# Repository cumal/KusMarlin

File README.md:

# Krotos3D

Custom [Marlin](https://github.com/MarlinFirmware/Marlin) firmware for [Krotos3d](https://kustomizit.com/build-your-own-3d-printer/) printer

## New Gcode
```
M777 - HW bed leveling
```
New custom gcode to use the 4-motor Z axis for bed leveling

## Remarkable commands
```
G28 - Auto Home
G29 - Bed Leveling
M80 - Power On PSU
M81 - Power Off PSU
M114 - Get Current Position
M420 - Bed Leveling State
M500 - Save Settings
M503 - Report Settings
M851 - XYZ Probe Offset
```

## Tips
```
M420 S1 - before printing enables bed leveling
M851 Z-X.XX - sets nozzle diff
```

## Configure nozzle height
```
M777 - HW bed leveling
G29 - Bed leveling
G28 Z - Home z at center
G91 - Relative positioning
G1 Z-0.1 - Move up the bed until it touches the nozzle
M114 - Get the Z height X.XX
M851 Z-X.XX - Set the nozzle height to X.XX
```

## Updated files

1. M777.cpp
   - Added custom gcode
2. pins_RAMPS.h
   - Added z axis motors pins
3. gcode.h
   - Added M777
4. gcode.cpp
   - Added 777
5. configuration.h
   - Updated e driver to drv8825
   - Z_MIN_ENDSTOP_INVERTING to true
   - Z_MIN_PROBE_ENDSTOP_INVERTING to true
   - DEFAULT_AXIS_STEPS_PER_UNIT to { 400, 400, 400, 98 }
   - DEFAULT_MAX_ACCELERATION to { 100, 50, 25, 10000 }
   - Update ACCELERATION
   - define USE_PROBE_FOR_Z_HOMING
   - define FIX_MOUNTED_PROBE

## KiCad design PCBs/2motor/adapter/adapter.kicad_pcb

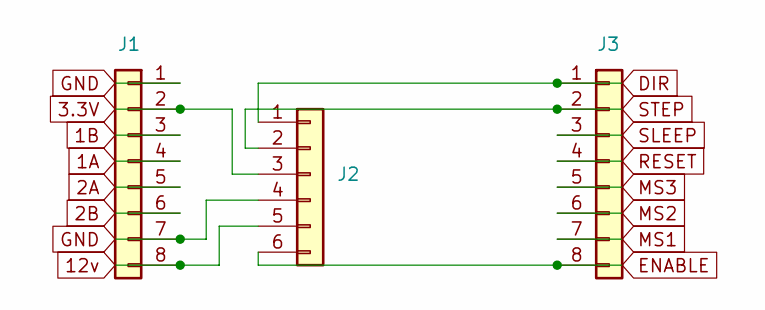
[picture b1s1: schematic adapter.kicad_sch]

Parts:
J1, J3: Conn_01x08; PinHeader_1x08_P2.54mm_Vertical
J2: Conn_01x06; PinSocket_1x06_P2.54mm_Vertical

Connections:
1A: J1.4
1B: J1.3
2A: J1.5
2B: J1.6
3.3V: J1.2, J2.3
12v: J1.8, J2.5
DIR: J2.1, J3.1
ENABLE: J2.6, J3.8
GND: J1.1, J1.7, J2.4
MS1: J3.7
MS2: J3.6
MS3: J3.5
RESET: J3.4
SLEEP: J3.3
STEP: J2.2, J3.2

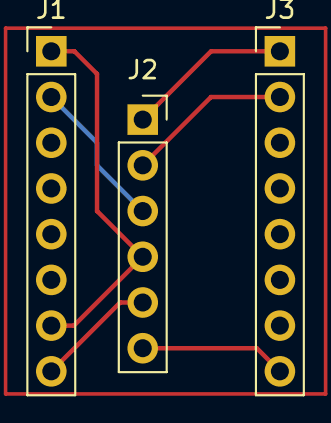
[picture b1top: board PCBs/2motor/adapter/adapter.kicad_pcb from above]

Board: 2 copper layers, 3 parts (0 on the bottom side), 6 nets.

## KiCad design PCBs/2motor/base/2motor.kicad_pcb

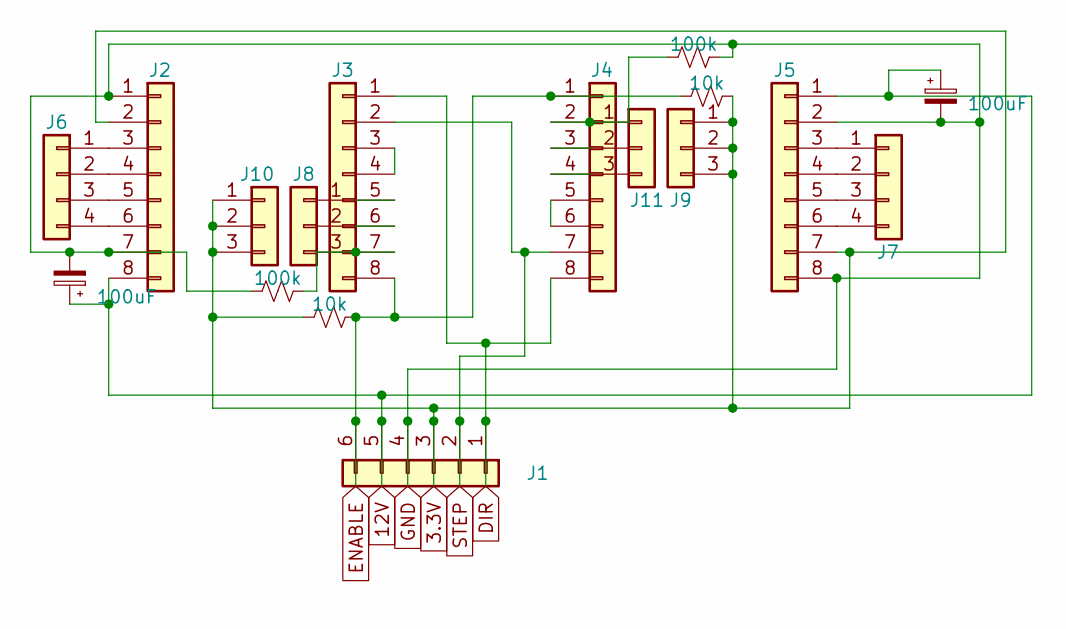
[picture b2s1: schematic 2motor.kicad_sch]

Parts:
C1, C2: 100uF; CP_Radial_D5.0mm_P2.50mm
J1: Conn_01x06; PinSocket_1x06_P2.54mm_Vertical
J2, J3, J4, J5: Conn_01x08; PinSocket_1x08_P2.54mm_Vertical
J6, J7: Conn_01x04; PinHeader_1x04_P2.54mm_Vertical
J8, J9, J10, J11: Conn_01x03; PinHeader_1x03_P2.54mm_Vertical
R1, R3: 100k; R_Axial_DIN0204_L3.6mm_D1.6mm_P7.62mm_Horizontal
R2, R4: 10k; R_Axial_DIN0204_L3.6mm_D1.6mm_P7.62mm_Horizontal

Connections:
3.3V: J1.3, J2.2, J5.7, J9.1, J9.2, J9.3, J10.1, J10.2, J10.3, R2.2, R4.1
12V: C1.1, C2.1, J1.5, J2.8, J5.1
DIR: J1.1, J3.1, J4.8
ENABLE: J1.6, J3.8, J4.1, R2.1, R4.2
GND: C1.2, C2.2, J1.4, J2.1, J2.7, J5.2, J5.8, R1.2, R3.1
unnamed: J2.3, J6.1
unnamed: J2.4, J6.2
unnamed: J2.5, J6.3
unnamed: J2.6, J6.4
unnamed: J3.3, J3.4
unnamed: J3.5, J8.1
unnamed: J3.6, J8.2
unnamed: J4.5, J4.6
unnamed: J5.3, J7.1
unnamed: J5.4, J7.2
unnamed: J5.5, J7.3
unnamed: J5.6, J7.4
unnamed: J3.7, J8.3, R1.1
unnamed: J4.3, J11.2
unnamed: J4.4, J11.3
unnamed: J4.2, J11.1, R3.2
STEP: J1.2, J3.2, J4.7

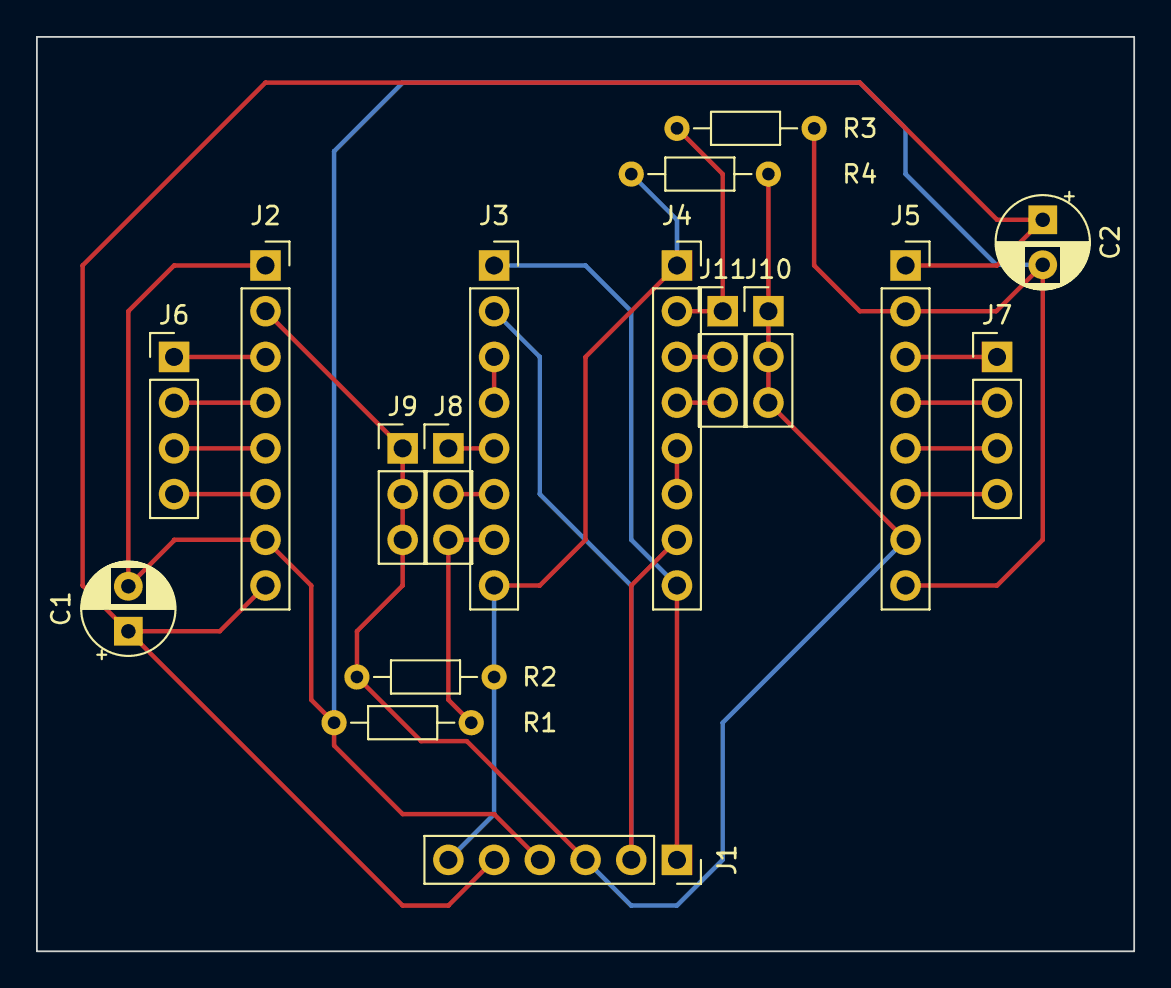
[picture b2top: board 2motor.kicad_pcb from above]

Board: 2 copper layers, 61.0 x 50.8 mm, 17 parts (0 on the bottom side), 22 nets.

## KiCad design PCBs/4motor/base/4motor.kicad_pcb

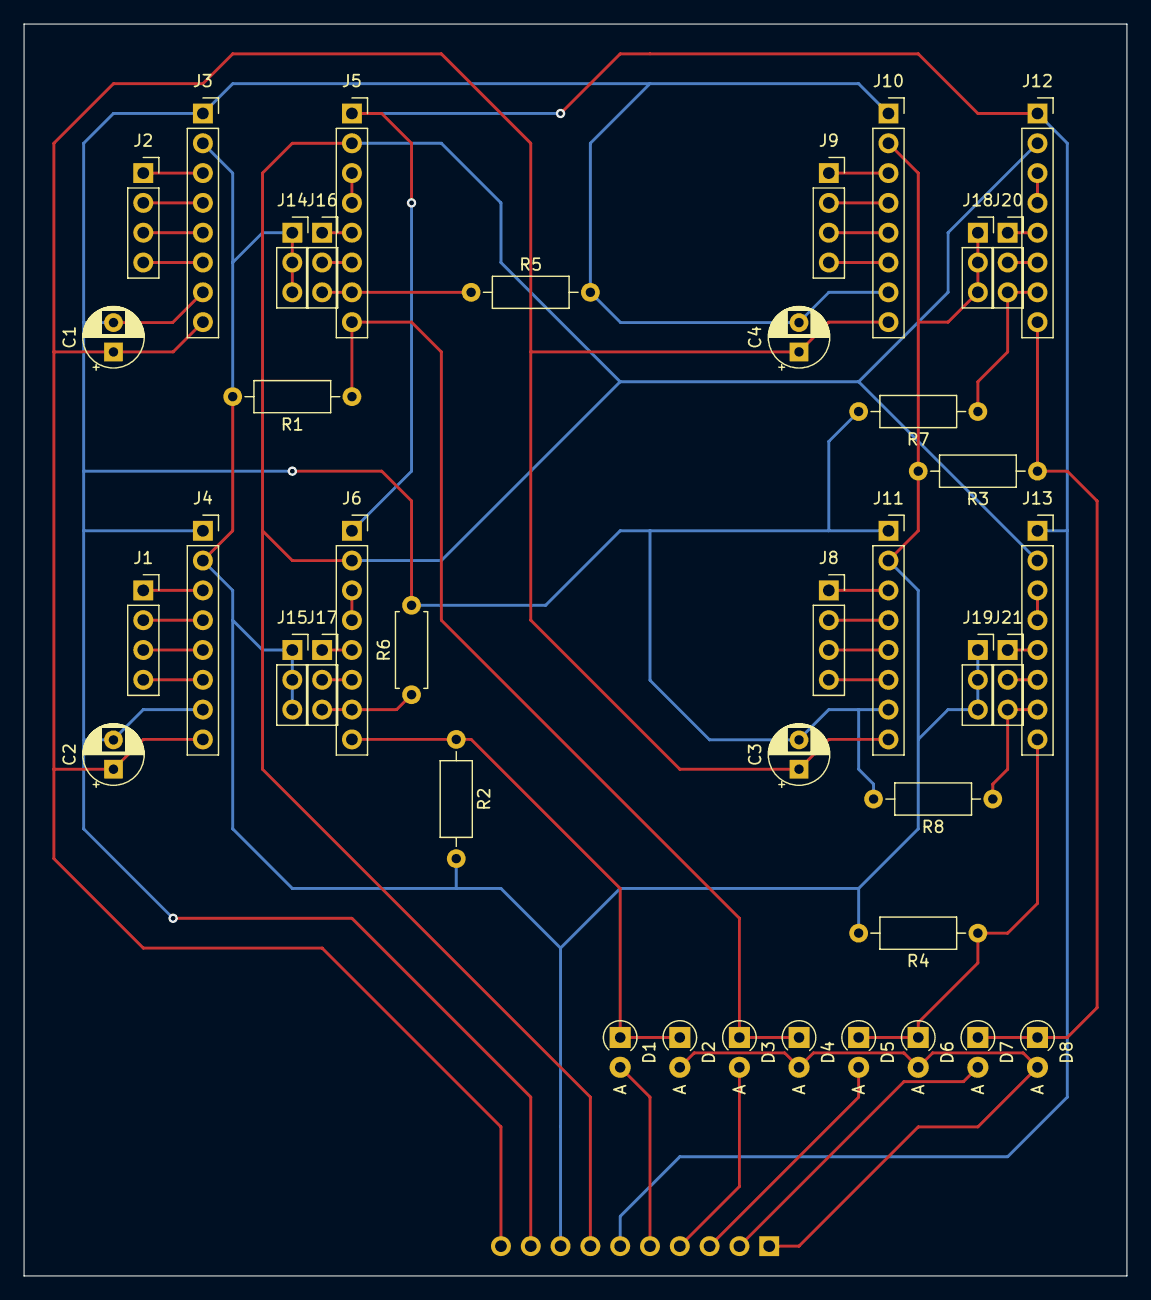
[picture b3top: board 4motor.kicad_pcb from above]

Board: 2 copper layers, 94.0 x 106.7 mm, 41 parts (1 on the bottom side), 46 nets.

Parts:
C1, C2, C3, C4: CP_Small; CP_Radial_D5.0mm_P2.50mm
D1, D2, D3, D4, D5, D6, D7, D8: D; D_A-405_P2.54mm_Vertical_AnodeUp
J1, J2, J8, J9: Conn_01x04_Male; PinSocket_1x04_P2.54mm_Vertical
J3, J4, J5, J6, J10, J11, J12, J13: Conn_01x08; PinSocket_1x08_P2.54mm_Vertical
J7: Conn_01x10; PinSocket_1x10_P2.54mm_Vertical
J14, J15, J16, J17, J18, J19, J20, J21: Conn_01x03; PinSocket_1x03_P2.54mm_Vertical
R1, R2, R3, R4, R5, R7, R8: R_Small_US; R_Axial_DIN0207_L6.3mm_D2.5mm_P10.16mm_Horizontal
R6: R_Small_US; R_Axial_DIN0207_L6.3mm_D2.5mm_P7.62mm_Horizontal

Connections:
3.3V: J3.2, J4.2, J7.8, J10.2, J11.2, J14.1, J14.2, J14.3, J15.1, J15.2, J15.3, J18.1, J18.2, J18.3, J19.1, J19.2, J19.3, R1.2, R2.2, R3.2, R4.2
12V: C1.1, C2.1, C3.1, C4.1, J3.8, J4.8, J7.10, J10.8, J11.8
Dir: J5.1, J6.1, J7.6, J12.1, J13.1
Enable1: D1.2 (A), J7.5
Enable2: D3.2 (A), J7.4
Enable3: D5.2 (A), J7.3
Enable4: D7.2 (A), J7.2
EnableAll: D2.2 (A), D4.2 (A), D6.2 (A), D8.2 (A), J7.1
GND: C1.2, C2.2, C3.2, C4.2, J3.1, J3.7, J4.1, J4.7, J7.9, J10.1, J10.7, J11.1, J11.7, R5.2, R6.2, R7.2, R8.2
unnamed: D1.1 (K), D2.1 (K), J6.8, R2.1
unnamed: D5.1 (K), D6.1 (K), J13.8, R4.1
unnamed: D7.1 (K), D8.1 (K), J12.8, R3.1
unnamed: J1.1, J4.3
unnamed: J1.3, J4.5
unnamed: J1.4, J4.6
unnamed: J2.1, J3.3
unnamed: J2.2, J3.4
unnamed: J2.3, J3.5
unnamed: J2.4, J3.6
unnamed: J1.2, J4.4
unnamed: J5.3, J5.4
unnamed: J5.5, J16.1
unnamed: D3.1 (K), D4.1 (K), J5.8, R1.1
unnamed: J6.3, J6.4
unnamed: J9.1, J10.3
unnamed: J9.2, J10.4
unnamed: J9.3, J10.5
unnamed: J9.4, J10.6
unnamed: J8.1, J11.3
unnamed: J8.2, J11.4
unnamed: J8.3, J11.5
unnamed: J8.4, J11.6
unnamed: J12.3, J12.4
unnamed: J12.5, J20.1
unnamed: J12.6, J20.2
unnamed: J12.7, J20.3, R7.1
unnamed: J13.3, J13.4
unnamed: J13.5, J21.1
unnamed: J13.6, J21.2
unnamed: J13.7, J21.3, R8.1
unnamed: J5.6, J16.2
unnamed: J5.7, J16.3, R5.1
unnamed: J6.5, J17.1
unnamed: J6.6, J17.2
unnamed: J6.7, J17.3, R6.1
Step: J5.2, J6.2, J7.7, J12.2, J13.2

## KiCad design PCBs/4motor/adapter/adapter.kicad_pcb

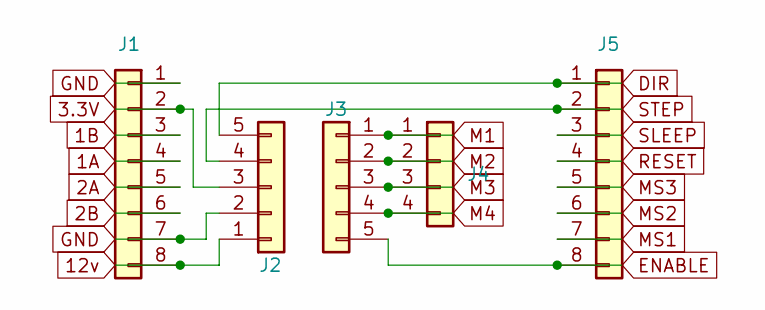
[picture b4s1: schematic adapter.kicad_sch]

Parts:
J1, J5: Conn_01x08; PinHeader_1x08_P2.54mm_Vertical
J2, J3: Conn_01x05; PinHeader_1x05_P2.54mm_Vertical
J4: Conn_01x04; PinHeader_1x04_P2.54mm_Vertical

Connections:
1A: J1.4
1B: J1.3
2A: J1.5
2B: J1.6
3.3V: J1.2, J2.3
12v: J1.8, J2.1
DIR: J2.5, J5.1
ENABLE: J3.5, J5.8
GND: J1.1, J1.7, J2.2
M1: J3.1, J4.1
M2: J3.2, J4.2
M3: J3.3, J4.3
M4: J3.4, J4.4
MS1: J5.7
MS2: J5.6
MS3: J5.5
RESET: J5.4
SLEEP: J5.3
STEP: J2.4, J5.2

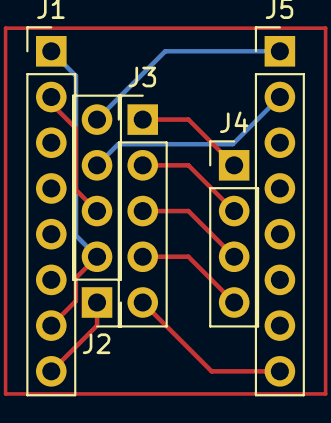
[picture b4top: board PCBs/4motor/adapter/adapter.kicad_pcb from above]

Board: 2 copper layers, 5 parts (0 on the bottom side), 10 nets.

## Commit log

2020-12-10 Fist commit
2020-12-10 Updated with custom config
2020-12-10 Order repo
2020-12-10 Added Readme
2020-12-10 Fixed errors
2020-12-10 Fix compilation
2020-12-10 Fixed compilation
2020-12-10 Updated pins
2020-12-11 Fixed hw bel leveling
2020-12-11 Updated config
2020-12-11 Added center height as 778
2020-12-11 Added z-probe offset
2020-12-16 Fixed timeout
2020-12-16 Fixed compilation errors
2020-12-16 Minor update
2021-01-03 Updated z feedrate
2021-01-03 Updated M777
2021-01-05 Fixed m777
2022-05-13 Cleaned gcodes
2022-05-13 Updated bedlevel
2022-05-23 Updated from tag 2.0.9.3
2024-12-16 Updatde custom gcode M777
2024-12-16 Updated from Martin v2.1.3 2024-12-16
2024-12-17 Add M777 to gcode.h
2024-12-17 Merged with custom config
2024-12-17 Added gitignore
2024-12-17 Updated floats to use ints
2024-12-17 Fixed calculations
2024-12-18 Minor update to reduce probe failings
2025-01-11 Update PCBs
